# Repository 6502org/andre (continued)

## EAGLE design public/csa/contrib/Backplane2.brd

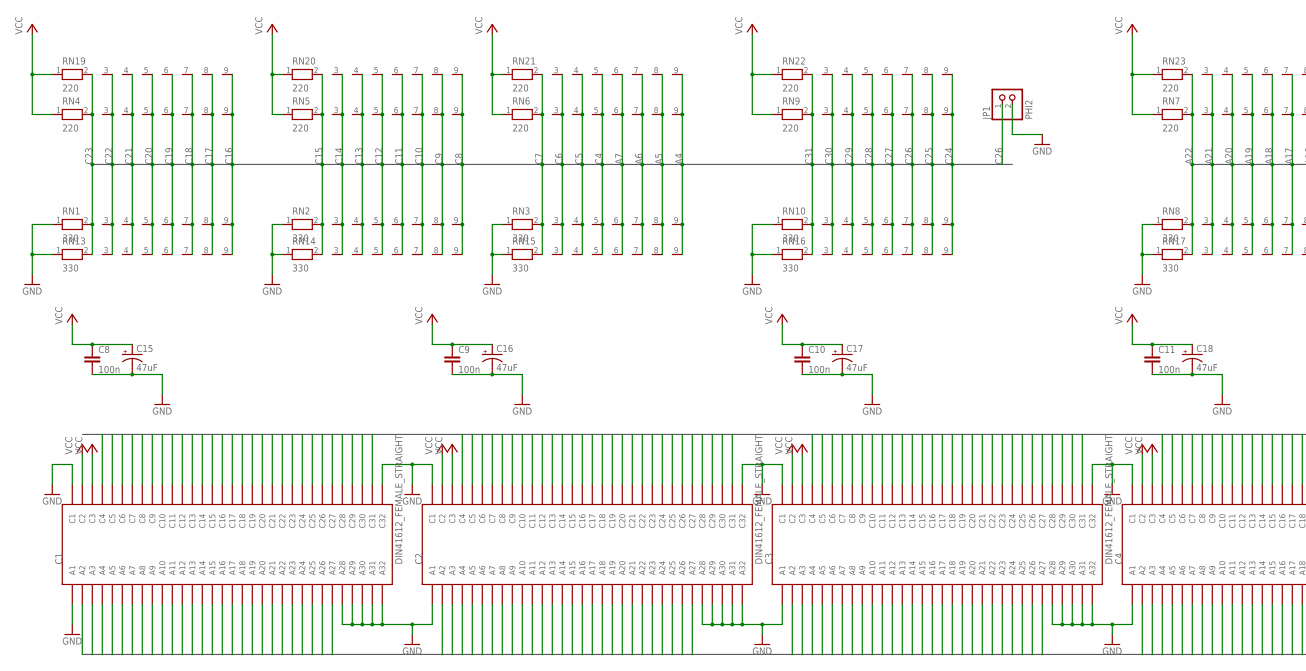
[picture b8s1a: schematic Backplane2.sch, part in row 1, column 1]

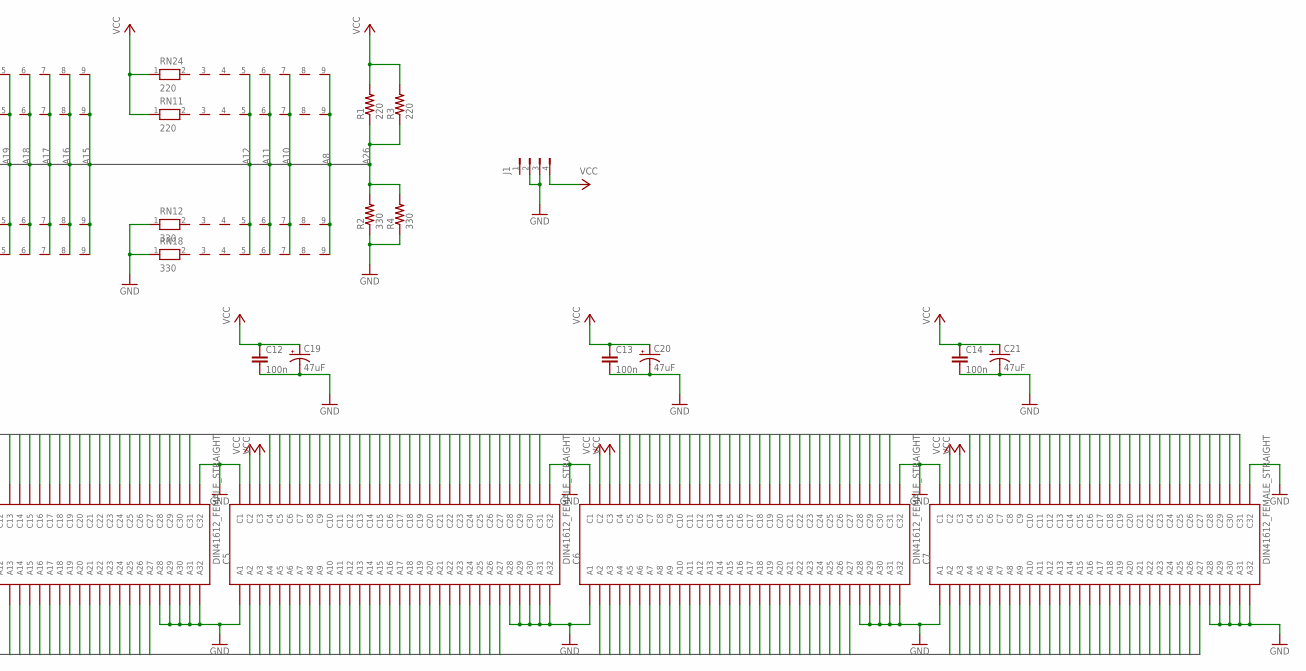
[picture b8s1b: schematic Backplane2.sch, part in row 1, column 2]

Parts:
C1, C2, C3, C4, C5, C6, C7: DIN41612_FEMALE_STRAIGHT
C8, C9, C10, C11, C12, C13, C14: 100n; C025-025X050
C15, C16, C17, C18, C19, C20, C21: 47uF; E2,5-7
J1: FLOPPY-4350211; 350211
JP1: PHI2; 1X02
R1, R3: 220; 0204/5
R2, R4: 330; 0204/5
RN1, RN2, RN3, RN8, RN10, RN12, RN13, RN14, RN15, RN16, RN17, RN18: 330; RN-9
RN4, RN5, RN6, RN7, RN9, RN11, RN19, RN20, RN21, RN22, RN23, RN24: 220; RN-9

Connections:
A2: C1.A2, C2.A2, C3.A2, C4.A2, C5.A2, C6.A2, C7.A2
A3: C1.A3, C2.A3, C3.A3, C4.A3, C5.A3, C6.A3, C7.A3
A4: C1.A4, C2.A4, C3.A4, C4.A4, C5.A4, C6.A4, C7.A4, RN3.9, RN6.9, RN15.9, RN21.9
A5: C1.A5, C2.A5, C3.A5, C4.A5, C5.A5, C6.A5, C7.A5, RN3.8, RN6.8, RN15.8, RN21.8
A6: C1.A6, C2.A6, C3.A6, C4.A6, C5.A6, C6.A6, C7.A6, RN3.7, RN6.7, RN15.7, RN21.7
A7: C1.A7, C2.A7, C3.A7, C4.A7, C5.A7, C6.A7, C7.A7, RN3.6, RN6.6, RN15.6, RN21.6
A8: C1.A8, C2.A8, C3.A8, C4.A8, C5.A8, C6.A8, C7.A8, RN11.9, RN12.9, RN18.9, RN24.9
A9: C1.A9, C2.A9, C3.A9, C4.A9, C5.A9, C6.A9, C7.A9
A10: C1.A10, C2.A10, C3.A10, C4.A10, C5.A10, C6.A10, C7.A10, RN11.7, RN12.7, RN18.7, RN24.7
A11: C1.A11, C2.A11, C3.A11, C4.A11, C5.A11, C6.A11, C7.A11, RN11.6, RN12.6, RN18.6, RN24.6
A12: C1.A12, C2.A12, C3.A12, C4.A12, C5.A12, C6.A12, C7.A12, RN11.5, RN12.5, RN18.5, RN24.5
A13: C1.A13, C2.A13, C3.A13, C4.A13, C5.A13, C6.A13, C7.A13
A14: C1.A14, C2.A14, C3.A14, C4.A14, C5.A14, C6.A14, C7.A14
A15: C1.A15, C2.A15, C3.A15, C4.A15, C5.A15, C6.A15, C7.A15, RN7.9, RN8.9, RN17.9, RN23.9
A16: C1.A16, C2.A16, C3.A16, C4.A16, C5.A16, C6.A16, C7.A16, RN7.8, RN8.8, RN17.8, RN23.8
A17: C1.A17, C2.A17, C3.A17, C4.A17, C5.A17, C6.A17, C7.A17, RN7.7, RN8.7, RN17.7, RN23.7
A18: C1.A18, C2.A18, C3.A18, C4.A18, C5.A18, C6.A18, C7.A18, RN7.6, RN8.6, RN17.6, RN23.6
A19: C1.A19, C2.A19, C3.A19, C4.A19, C5.A19, C6.A19, C7.A19, RN7.5, RN8.5, RN17.5, RN23.5
A20: C1.A20, C2.A20, C3.A20, C4.A20, C5.A20, C6.A20, C7.A20, RN7.4, RN8.4, RN17.4, RN23.4
A21: C1.A21, C2.A21, C3.A21, C4.A21, C5.A21, C6.A21, C7.A21, RN7.3, RN8.3, RN17.3, RN23.3
A22: C1.A22, C2.A22, C3.A22, C4.A22, C5.A22, C6.A22, C7.A22, RN7.2, RN8.2, RN17.2, RN23.2
A23: C1.A23, C2.A23, C3.A23, C4.A23, C5.A23, C6.A23, C7.A23
A24: C1.A24, C2.A24, C3.A24, C4.A24, C5.A24, C6.A24, C7.A24
A25: C1.A25, C2.A25, C3.A25, C4.A25, C5.A25, C6.A25, C7.A25
A26: C1.A26, C2.A26, C3.A26, C4.A26, C5.A26, C6.A26, C7.A26, R1.1, R2.2, R3.1, R4.2
A27: C1.A27, C2.A27, C3.A27, C4.A27, C5.A27, C6.A27, C7.A27
C4: C1.C4, C2.C4, C3.C4, C4.C4, C5.C4, C6.C4, C7.C4, RN3.5, RN6.5, RN15.5, RN21.5
C5: C1.C5, C2.C5, C3.C5, C4.C5, C5.C5, C6.C5, C7.C5, RN3.4, RN6.4, RN15.4, RN21.4
C6: C1.C6, C2.C6, C3.C6, C4.C6, C5.C6, C6.C6, C7.C6, RN3.3, RN6.3, RN15.3, RN21.3
C7: C1.C7, C2.C7, C3.C7, C4.C7, C5.C7, C6.C7, C7.C7, RN3.2, RN6.2, RN15.2, RN21.2
C8: C1.C8, C2.C8, C3.C8, C4.C8, C5.C8, C6.C8, C7.C8, RN2.9, RN5.9, RN14.9, RN20.9
C9: C1.C9, C2.C9, C3.C9, C4.C9, C5.C9, C6.C9, C7.C9, RN2.8, RN5.8, RN14.8, RN20.8
C10: C1.C10, C2.C10, C3.C10, C4.C10, C5.C10, C6.C10, C7.C10, RN2.7, RN5.7, RN14.7, RN20.7
C11: C1.C11, C2.C11, C3.C11, C4.C11, C5.C11, C6.C11, C7.C11, RN2.6, RN5.6, RN14.6, RN20.6
C12: C1.C12, C2.C12, C3.C12, C4.C12, C5.C12, C6.C12, C7.C12, RN2.5, RN5.5, RN14.5, RN20.5
C13: C1.C13, C2.C13, C3.C13, C4.C13, C5.C13, C6.C13, C7.C13, RN2.4, RN5.4, RN14.4, RN20.4
C14: C1.C14, C2.C14, C3.C14, C4.C14, C5.C14, C6.C14, C7.C14, RN2.3, RN5.3, RN14.3, RN20.3
C15: C1.C15, C2.C15, C3.C15, C4.C15, C5.C15, C6.C15, C7.C15, RN2.2, RN5.2, RN14.2, RN20.2
C16: C1.C16, C2.C16, C3.C16, C4.C16, C5.C16, C6.C16, C7.C16, RN1.9, RN4.9, RN13.9, RN19.9
C17: C1.C17, C2.C17, C3.C17, C4.C17, C5.C17, C6.C17, C7.C17, RN1.8, RN4.8, RN13.8, RN19.8
C18: C1.C18, C2.C18, C3.C18, C4.C18, C5.C18, C6.C18, C7.C18, RN1.7, RN4.7, RN13.7, RN19.7
C19: C1.C19, C2.C19, C3.C19, C4.C19, C5.C19, C6.C19, C7.C19, RN1.6, RN4.6, RN13.6, RN19.6
C20: C1.C20, C2.C20, C3.C20, C4.C20, C5.C20, C6.C20, C7.C20, RN1.5, RN4.5, RN13.5, RN19.5
C21: C1.C21, C2.C21, C3.C21, C4.C21, C5.C21, C6.C21, C7.C21, RN1.4, RN4.4, RN13.4, RN19.4
C22: C1.C22, C2.C22, C3.C22, C4.C22, C5.C22, C6.C22, C7.C22, RN1.3, RN4.3, RN13.3, RN19.3
C23: C1.C23, C2.C23, C3.C23, C4.C23, C5.C23, C6.C23, C7.C23, RN1.2, RN4.2, RN13.2, RN19.2
C24: C1.C24, C2.C24, C3.C24, C4.C24, C5.C24, C6.C24, C7.C24, RN9.9, RN10.9, RN16.9, RN22.9
C25: C1.C25, C2.C25, C3.C25, C4.C25, C5.C25, C6.C25, C7.C25, RN9.8, RN10.8, RN16.8, RN22.8
C26: C1.C26, C2.C26, C3.C26, C4.C26, C5.C26, C6.C26, C7.C26, JP1.1, RN9.7, RN10.7, RN16.7, RN22.7
C27: C1.C27, C2.C27, C3.C27, C4.C27, C5.C27, C6.C27, C7.C27, RN9.6, RN10.6, RN16.6, RN22.6
C28: C1.C28, C2.C28, C3.C28, C4.C28, C5.C28, C6.C28, C7.C28, RN9.5, RN10.5, RN16.5, RN22.5
C29: C1.C29, C2.C29, C3.C29, C4.C29, C5.C29, C6.C29, C7.C29, RN9.4, RN10.4, RN16.4, RN22.4
C30: C1.C30, C2.C30, C3.C30, C4.C30, C5.C30, C6.C30, C7.C30, RN9.3, RN10.3, RN16.3, RN22.3
C31: C1.C31, C2.C31, C3.C31, C4.C31, C5.C31, C6.C31, C7.C31, RN9.2, RN10.2, RN16.2, RN22.2
GND: C1.A1, C1.A28, C1.A29, C1.A30, C1.A31, C1.A32, C1.C1, C1.C32, C2.A1, C2.A28, C2.A29, C2.A30, C2.A31, C2.A32, C2.C1, C2.C32, C3.A1, C3.A28, C3.A29, C3.A30, C3.A31, C3.A32, C3.C1, C3.C32, C4.A1, C4.A28, C4.A29, C4.A30, C4.A31, C4.A32, C4.C1, C4.C32, C5.A1, C5.A28, C5.A29, C5.A30, C5.A31, C5.A32, C5.C1, C5.C32, C6.A1, C6.A28, C6.A29, C6.A30, C6.A31, C6.A32, C6.C1, C6.C32, C7.A1, C7.A28, C7.A29, C7.A30, C7.A31, C7.A32, C7.C1, C7.C32, C8.2, C9.2, C10.2, C11.2, C12.2, C13.2, C14.2, C15.-, C16.-, C17.-, C18.-, C19.-, C20.-, C21.-, J1.2, J1.3, JP1.2, R2.1, R4.1, RN1.1, RN2.1, RN3.1, RN8.1, RN10.1, RN12.1, RN13.1, RN14.1, RN15.1, RN16.1, RN17.1, RN18.1
VCC: C1.C2, C1.C3, C2.C2, C2.C3, C3.C2, C3.C3, C4.C2, C4.C3, C5.C2, C5.C3, C6.C2, C6.C3, C7.C2, C7.C3, C8.1, C9.1, C10.1, C11.1, C12.1, C13.1, C14.1, C15.+, C16.+, C17.+, C18.+, C19.+, C20.+, C21.+, J1.4, R1.2, R3.2, RN4.1, RN5.1, RN6.1, RN7.1, RN9.1, RN11.1, RN19.1, RN20.1, RN21.1, RN22.1, RN23.1, RN24.1

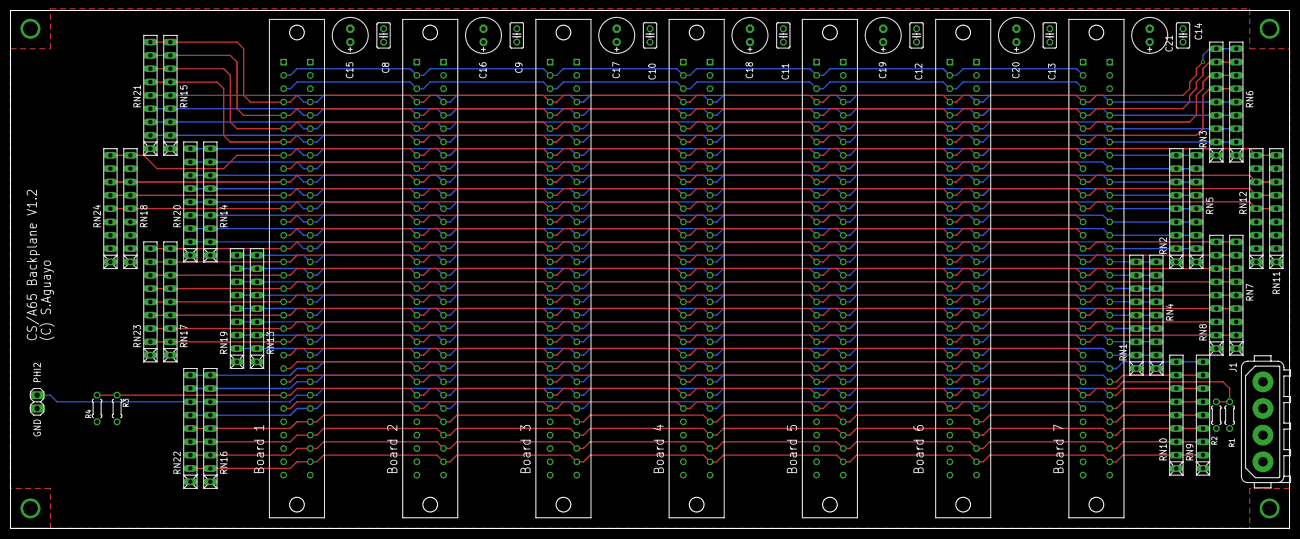
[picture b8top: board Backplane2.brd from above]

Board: 2 copper layers, 243.8 x 98.7 mm, 51 parts (0 on the bottom side), 56 nets.

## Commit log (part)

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2010-09-23 add further 65k project discussions
2010-09-26 more work on the 65k project
2010-09-28 Update CSA CPU816 V2.0B to include RDY protection resistor
2010-10-10 move 65k to top level
2010-10-10 remove 65k from lower level
2010-10-10 adv65 update
2010-10-10 add twisties
2010-10-10 Small design changes (twisities, min/max link)
2010-10-18 hide blitter
2010-10-20 remove blitter from public menu
2010-10-23 prepare to publish 65k
2010-10-23 publish the 65k project
2010-11-16 Publish some 65k work before it decays...
2010-11-28 Some PETindex updates
2010-12-19 added link to NO PETS ALLOWED demo on the petindex sw page
2010-12-20 rework of the CRTC pages
2010-12-22 Updated my CSA CPU816v2 board
2010-12-22 update 65k specs - add NF prefix bit
2010-12-28 65k update, csa ramdisk v2.0c
2010-12-31 Update (year end) of 65k, CSA Ramdisk
2011-01-04 add csa ethernet board
2011-01-09 update etholi, ramdisk, term
2011-01-09 final touch up for next release
2011-01-09 new web site revision
2011-01-11 new version etholi
2011-01-13 add petnet section
2011-01-15 new version, added PET on the 'Net
2011-03-06 blitter, usb, spi update
2011-04-22 new published release, adding a USB card and stack to the CS/A
2011-04-23 add petindex 8032sk page
2011-04-23 added petindex languages page
2011-04-24 fix a history generation bug in the xslt, make Twitter link external, add 8032sk page for my own 8032sk
2011-04-29 Add blitter board
2011-04-30 updated 65k
2011-05-01 65k update, publish CS/A blitter
2012-01-03 add spi dir
2012-01-04 moved spi65b into spi folder
2012-01-04 som emove
2012-01-04 more moves
2012-01-04 cleanup
2012-01-04 New tag with some updates, and social bookmarking
2012-04-12 new tag with docs for the af65002
2012-04-29 copy process for 65002 docs into web page
2012-04-30 fixed the generation process (was mangling up menu entries af65002 and 65002)
2012-05-06 Design update, update af65002 specs
2012-05-06 two small bug fixes
2012-10-26 Fix spelling
2012-10-26 New tag to test the deployment machinery
2013-01-04 Some updates, esp. the xslt processor changed (from xsltproc to xsl-c)
2013-01-06 Add usb65, xd2031 and some link fixes
2013-01-11 add missing picture
2013-01-13 added drivers to netusb2, add viaspi 1.1
2013-01-26 Move spi65b up to top level
2013-04-14 new responsive web design
2013-05-03 new release, small fixes
2013-10-13 Add video links to YT demos, add CBMUSB interface
2013-11-02 Update CRTC pages
2013-11-03 update gallery web design
2013-11-03 Add last modified date for each page
2013-11-03 Add last modified date for each page (fix)
2013-11-03 new web tag
2013-11-09 web style update
2013-11-10 updated web design
2013-11-10 Add missing image sources
2013-11-16 remove Ed's name, add some advanced links
2013-11-17 updated 65002 docs
2013-11-17 updated 65002 docs, fix pet816 web layout
2013-12-30 minor updates; added emulation section
2014-08-11 linked extrapages, updated video on pet816
2014-08-11 move pet816 up one level
2014-08-11 More updates
2014-08-22 new version of the site
2014-11-09 add links to bezels and labels
2015-01-06 update domain
2015-01-06 shariff test
2015-02-01 new version
2015-08-04 check for xsltproc so runs on both SuSE laptop and kubuntu
2015-08-04 include yui-compressor in repo
2015-08-04 Update last mod dates from last commit date
2015-09-20 remove old toolset
2015-09-20 updated some links, shariff config
2015-09-20 shariff config
2015-09-20 shariff config - remove non-existing backends
2015-09-25 trigger deploy
2015-10-11 small update and test for commit
2015-10-11 fix link
2016-04-24 small updates
2016-04-24 new tag
2016-04-25 enable shariff
2017-07-17 added contrib to CSA, diag clip to petindex (incomplete)
2017-07-23 Add PET diag clip page
2017-07-23 cleanup old socialshare privacy
2017-07-23 cleanup scripts
2017-07-23 small metadata update
2017-07-23 Update scripts
2017-07-23 Update, esp. PET diag clip, and javascript cleanup
2017-08-13 Update 1st version of PET diagnostic cartridge
2017-08-13 Added backplane
2017-08-13 Update index
2017-08-13 Add kernal mod link
2017-08-13 script trial
2017-08-13 trial
2017-08-13 test
2017-08-13 use uncompressed scripts in index2
2017-08-13 Fix javascript for search box
2017-08-13 update shariff
2017-08-13 test new shariff
2017-08-13 fix css link; add link to discussion of PET prototypes
2017-08-13 rm shariff backend
2017-08-14 test bx shariff URL
2017-08-14 update shariff URL
2017-08-27 changed shariff services
2017-08-27 Publish with added shariff services
2017-08-29 Added RS232 info to the PETindex
2017-08-29 Update with RS232 info in the PET index
2017-09-29 A larger number of petindex updates
2017-10-15 updated and added Links
2017-10-15 Update Oct 2017
2017-10-15 Add missing news message
2017-10-15 update copyright year
2017-10-21 Small link update adv65
2018-04-01 Change page creation to use git log for last modified date. Also fix share links. Note: need to remember to commit source first before page creation, or date will have previous commit date...
2018-04-01 Fix last mod date for index.html
2018-04-01 Add links to Steve's graphics page
2018-04-01 Add links to Steve's graphics pages and spacetaxi's disk drive page
2018-04-01 Add changelog
2018-04-01 create pages
2018-12-29 Small changes
2019-08-30 update on sneak, first csa prep on 30th anniversary
2019-08-31 30th anniversary of the CS/A computer with an updated gallery
2019-08-31 update last modified
2019-08-31 first part of XS1541 page
2019-08-31 publish XS1541 initial page
2019-09-01 small image sizes for CSA gallery
2019-09-01 small update flashing xs1541 firmware
2020-05-02 update killer poke article
2020-05-02 remove shariff as server side is broken
2020-05-02 added some peripherals on petindex
2020-06-01 update PET 4.0 ROM disassembly link
2020-10-29 Update Oct. 2020 on PETindex
2020-10-29 update links
2020-10-29 fix news
2020-10-29 fix more links, teaser layout
2020-10-29 last mod date
2020-10-29 typo, add the L-Star
2020-10-29 clarification on 2332 ROMs
2021-09-13 Add Micro-PET
2021-09-13 tools update
2021-09-13 update dates
2021-10-17 Update CSA VDC and BIOS boards
2021-10-18 finalize vdc 1.4d
2021-10-18 various updates for CS/A, and GeckOS github link
2021-10-25 add missing eagle files petio 1.1e
2021-11-21 add petio 1.2b
2021-12-10 Fix pin J in user port pinout
2021-12-29 new revision of DRVIO
2021-12-29 Fix pinout of IEEE port, J was wrongly marked as K
2021-12-29 update CS/A boards
2021-12-29 fix IEEE layout doc
2021-12-29 last modified date
2021-12-29 added CS/A extender board
2022-03-13 add PETIO 1.3A board
2022-03-13 last update date
2023-01-08 update for 2023
2023-01-08 introduce the ultmate pet
2023-02-05 add link
2023-02-05 update modified dates
2023-07-23 added some links on the petindex
2023-07-23 fix last modified dates
2023-07-23 update jquery
2023-08-27 add short CS/A bus connector spec
2023-08-27 update last update date
2023-08-27 fix menu for updated bus specs
2023-08-27 fix Jquery update
2023-12-13 various updates, mostly SID, UltraCPU
2023-12-13 get HTML out of quirks mode
2024-02-03 update ultimate PET page
2024-02-03 add csa/iecuart board
2024-02-03 make MMC/SD-Card visible in search for SPI keyword
2024-02-03 remove Twitter link as it's dead, add Mastodon and Bluesky
2024-02-03 rename Ultimate PET to Ulti-PET
2024-02-03 change more Ultimate references
2024-02-03 typo
2024-02-06 update GeckOS page to 2.1.1 - last mod dates
2024-02-06 update/add GeckOS YT videos
2024-02-14 add petio 1.3b
2024-02-14 add csa petio 1.3b layout explainer
2024-02-15 small updates, links between Micro-/Ulti-/CSA-PETs
2024-09-21 add link to new xcbm development
2024-09-21 modified date
2024-09-21 CS/A bus comments
2024-09-21 commit html with modified date
2024-09-21 updates on ultipet and geckos
2024-09-21 updated versions of geckos, ultipet
2024-09-21 link ultrabus to github
2024-09-21 potential new header
2024-10-24 update link colour
2024-10-30 update ultipet status
2024-10-30 modified dates
2026-01-05 some link updates, added BDOS page
2026-01-05 last mod dates
2026-01-05 update copyright
2026-01-06 added PETindex video page
2026-01-06 add link to PET repair document
2026-01-18 add the econopet
2026-02-27 update o65 page to link to the new file format master on github
2026-02-27 version number
2026-02-27 updated copyright date on o65 page
2026-05-12 update ultipet page; add ultipet link to the hot! section
